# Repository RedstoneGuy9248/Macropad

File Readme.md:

# Ridhim's Macropad
Ridhim's Macropad is a 9-key macropad with a EC11 rotary encoder running on an RPi Pico. (Made for Hack Club Fallout)

## Features:
- Cool looking case
- EC11 Rotary Encoder as a volume knob
- 9 Keys (Reprogrammable in Python)
- Connects using Micro-USB

### why?
I made this project as a bit of a more complex next project, compared to my [previous hardware project](https://github.com/RedstoneGuy9248/weatherStation), as i barely have any hardware experience and need practice to be able to build actual complex ones. (also for fallout lol). From this, I've learnt the basics of how to design PCBs in KiCAD, re-learnt Fusion 360 after like 4 years, and also understood a lot about how hardware made to like actual complete products are made. 

## Assembly:
- Snap the switches into the plate
- Then the switches, diodes, rotary encoder, and RPi Pico should be soldered onto the pcb acccording to the schematic. 
- Place the plate with the pcb attached underneath it into the base and fit the micro usb port into its hole
- Place the top part, and then insert 4 M3*20mm screws into the holes and secure underneath with nuts
- Insert keycaps onto switches and dial onto rotary encoder

## Setup
- [Install CircuitPython on the RPi Pico](https://learn.adafruit.com/welcome-to-circuitpython/installing-circuitpython)
- Get an up to date copy of [KMK](https://github.com/KMKfw/kmk_firmware/archive/refs/heads/main.zip)
- Unzip it and drag the contents into the root of the usb drive corresponding to the RPi Pico
- Copy the main.py file from firmware/ of this repo into the same root folder

## Schematic

## PCB

## Bill Of Materials

The BOM is available [here](/BOM.csv)

## Zine

(The PDF is available [here](/Ridhim%27s%20Macropad%20Zine.pdf))

## Note:

There are 2 variants of the plate available, one has a thickness of 1.5mm and the other is 3mm. The 3mm is the main one as it is the size specified in the Hackpad guide, and a 1.5mm 3D Printed plate would be very fragile.

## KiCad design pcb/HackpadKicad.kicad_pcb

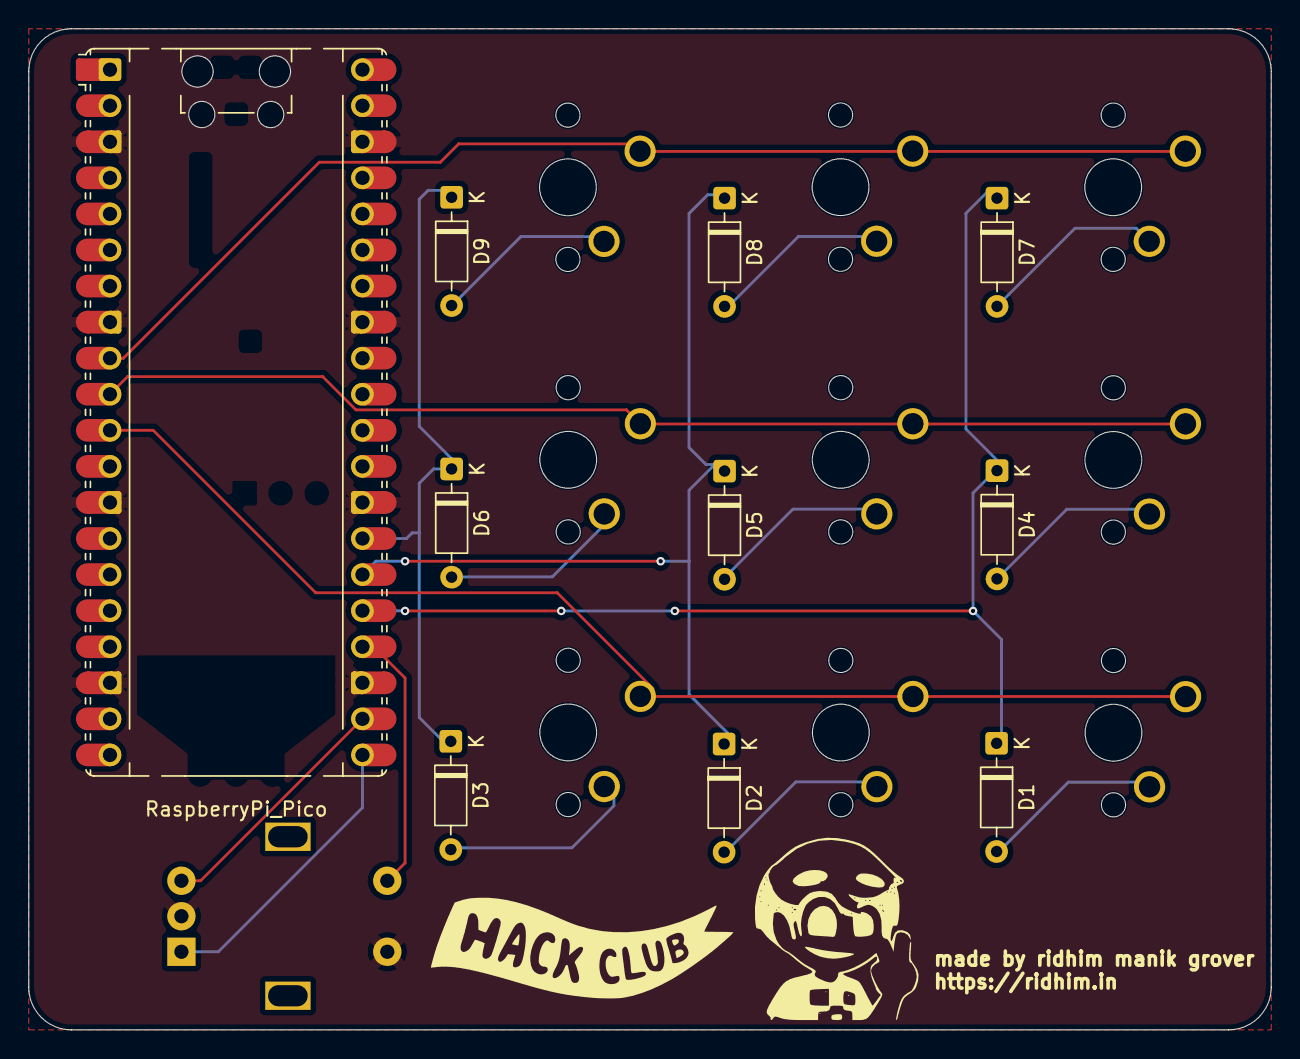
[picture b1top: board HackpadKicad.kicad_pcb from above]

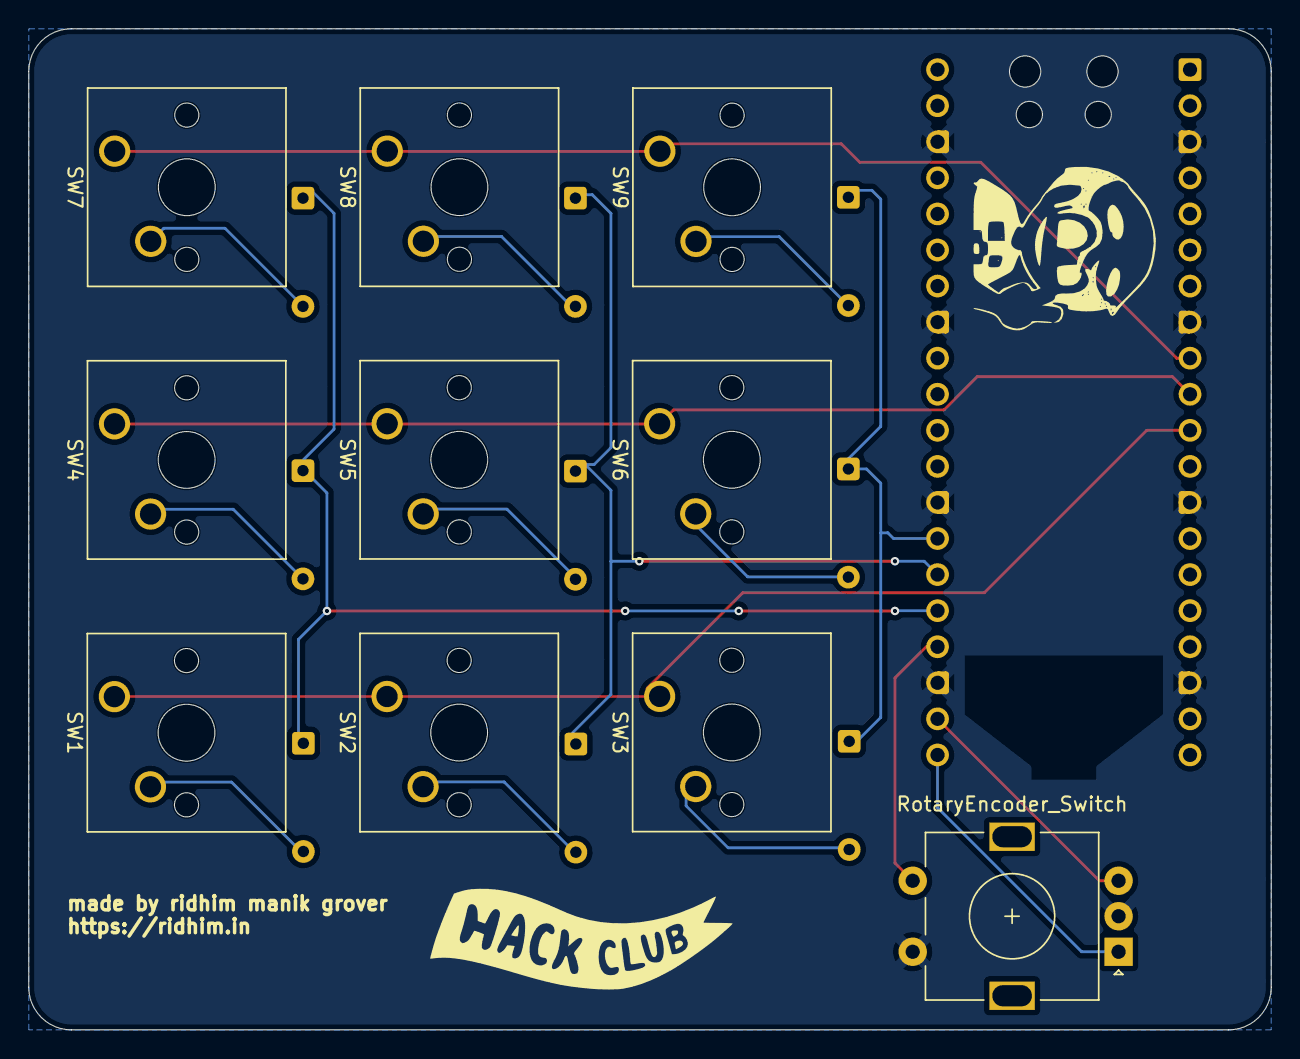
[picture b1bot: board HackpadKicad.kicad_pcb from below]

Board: 2 copper layers, 87.5 x 70.5 mm, 20 parts (10 on the bottom side), 19 nets.

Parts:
A1: RaspberryPi_Pico; RaspberryPi_Pico_Common_Unspecified
D1, D2, D3, D4, D5, D6, D7, D8, D9: 1N914; D_DO-35_SOD27_P7.62mm_Horizontal
SW1, SW2, SW3, SW4, SW5, SW6, SW7, SW8, SW9: SW_Push; SW_Cherry_MX_1.00u_PCB
SW10: RotaryEncoder_Switch; RotaryEncoder_Alps_EC11E-Switch_Vertical_H20mm

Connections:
GND: A1.3 (GND), A1.8 (GND), A1.13 (GND), A1.18 (GND), A1.23 (GND), A1.28 (GND), A1.33 (AGND), A1.38 (GND), SW10.C, SW10.S2
unnamed: A1.9 (GPIO6), SW7.1, SW8.1, SW9.1
unnamed: A1.10 (GPIO7), SW4.1, SW5.1, SW6.1
unnamed: A1.11 (GPIO8), SW1.1, SW2.1, SW3.1
unnamed: A1.21 (GPIO16), SW10.A
unnamed: A1.22 (GPIO17), SW10.B
unnamed: A1.24 (GPIO18), SW10.S1
unnamed: A1.25 (GPIO19), D1.1 (K), D4.1 (K), D7.1 (K)
unnamed: A1.26 (GPIO20), D2.1 (K), D5.1 (K), D8.1 (K)
unnamed: A1.27 (GPIO21), D3.1 (K), D6.1 (K), D9.1 (K)
unnamed: D1.2 (A), SW1.2
unnamed: D2.2 (A), SW2.2
unnamed: D3.2 (A), SW3.2
unnamed: D4.2 (A), SW4.2
unnamed: D5.2 (A), SW5.2
unnamed: D6.2 (A), SW6.2
unnamed: D7.2 (A), SW7.2
unnamed: D8.2 (A), SW8.2
unnamed: D9.2 (A), SW9.2

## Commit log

2026-04-18 Add initial README for Ridhim's Macropad
2026-04-18 Rename assets
2026-04-18 Update Readme with images and extra details
2026-04-18 Add BOM
2026-04-18 Update Readme with plate variant information
2026-04-18 rename firmware folder, update readme
2026-04-25 fix pcb clipping enclosure, filet pcb corners, add zine and why to readme
2026-04-25 fix errors in readme
